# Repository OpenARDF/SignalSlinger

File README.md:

# SignalSlinger

SignalSlinger is an open-source 80-meter radio orienteering (ARDF) transmitter kit for the 3.5 MHz to 3.7 MHz amateur band. It supports classic, sprint, and foxoring events, with a high-accuracy real-time clock for synchronized transmissions and scheduled start and finish times.

## Product Photo

## Documentation

* [User Manual](https://docs.google.com/document/d/1eX7xH3cDyRNS-MVg13EojpP8IB8bDgrdszM48J0sn7k/edit?usp=sharing)
* [Bill of Material](https://docs.google.com/spreadsheets/d/182rCsEmR_KNoESYd0NLeVXOi867AKD0zTovbhvcYbqc/edit?usp=sharing)
* [GitHub Releases](https://github.com/OpenARDF/SignalSlinger/releases)

## Availability

SignalSlinger is available in kit form from Backwoods Orienteering Klub. [Order the SignalSlinger Transmitter Kit](https://backwoodsok.org/store/SignalSlinger-Transmitter-Kit-p799230332) or visit the product page for current pricing, availability, shipping information, and kit details.

## Updating Software

This `main` branch corresponds to the current stable firmware release. Download the update file that matches your hardware revision:

* `SignalSlinger-Update-v2.1.0-HW-3.5.hex`
* `SignalSlinger-Update-v2.1.0-HW-3.4.hex`

Use SerialSlinger for normal updates on devices that already support software updates. For first-time bootloader setup, use the matching complete release bundle and an approved programmer over the board's UPDI programming header (`P101`). Always choose the file that matches your hardware revision, and do not modify fuses or disable UPDI outside the documented setup flow.

For complete programming steps, setup-bundle usage, and hardware connection details, see the [User Manual](https://docs.google.com/document/d/1eX7xH3cDyRNS-MVg13EojpP8IB8bDgrdszM48J0sn7k/edit?usp=sharing). If you want current firmware and software development instead of the stable public release, use `Development1`. KiCad schematic, PCB, library, simulation, and model work is collected separately on `Development1-KiCad`. `main` remains linear, while collector pull requests use merge commits so topic and synchronized `main` ancestry are preserved; after a promotion, verify each focused synchronization topic with `just collector-sync-check <collector>`.

## Firmware Development

Firmware source and build scripts live in [`Software/AVR128DA28`](Software/AVR128DA28).

For the current development workflow, start here:

* [`Software/AVR128DA28/CODEX_WORKFLOW.md`](Software/AVR128DA28/CODEX_WORKFLOW.md) for branch and patch-verification expectations
* [`Software/AVR128DA28/RELEASE_WORKFLOW.md`](Software/AVR128DA28/RELEASE_WORKFLOW.md) for release preparation and dual-target asset checks
* [`Software/AVR128DA28/build-firmware.ps1`](Software/AVR128DA28/build-firmware.ps1) for the standard local firmware build
* [`Software/AVR128DA28/verify-firmware-hashes.ps1`](Software/AVR128DA28/verify-firmware-hashes.ps1) for dual-target `.hex` build and SHA256 verification

## Related Projects

* [SignalStreamer](https://github.com/OpenARDF/SignalStreamer), a matching antenna
* [SignalSnagger](https://github.com/OpenARDF/SignalSnagger), a companion receiver project
* [SerialSlinger](https://github.com/OpenARDF/SerialSlinger), a serial terminal and logging companion for SignalSlinger configuration and monitoring

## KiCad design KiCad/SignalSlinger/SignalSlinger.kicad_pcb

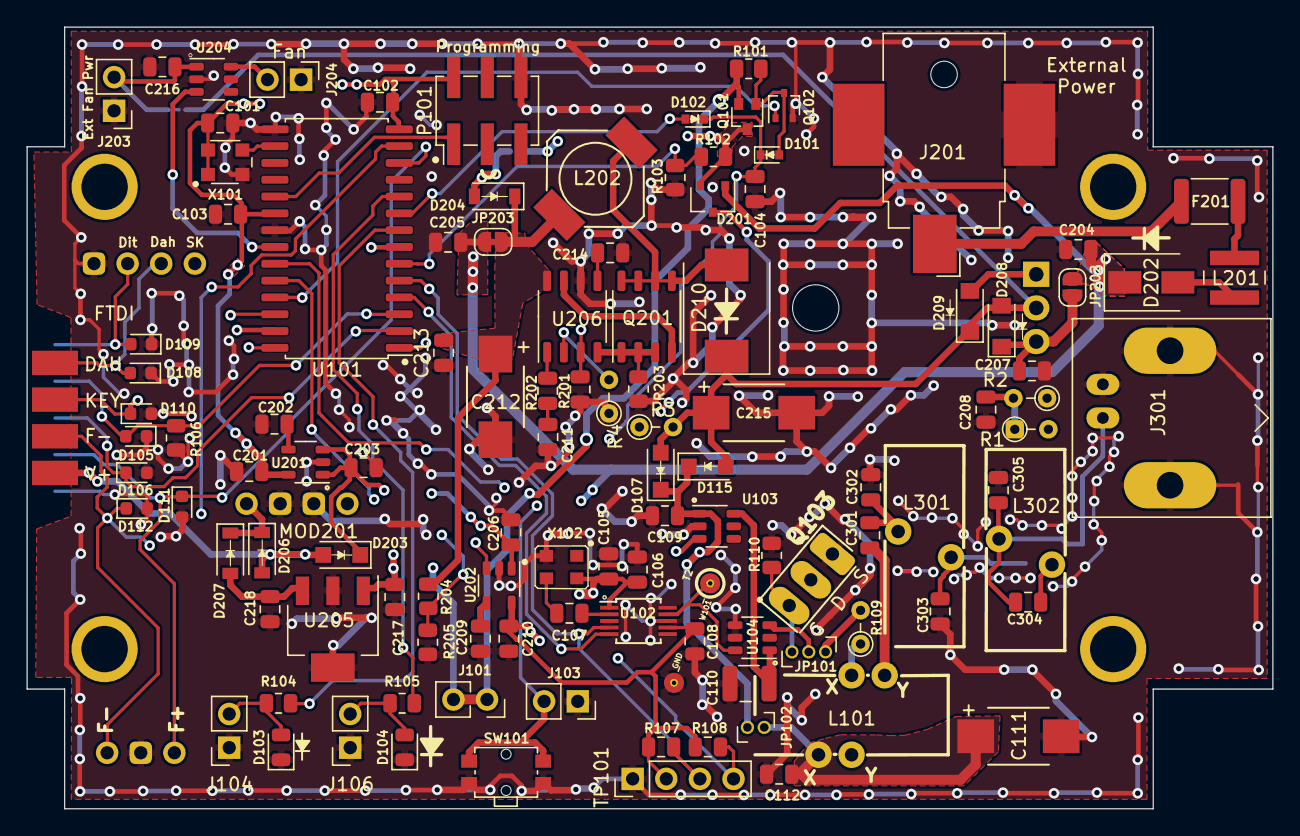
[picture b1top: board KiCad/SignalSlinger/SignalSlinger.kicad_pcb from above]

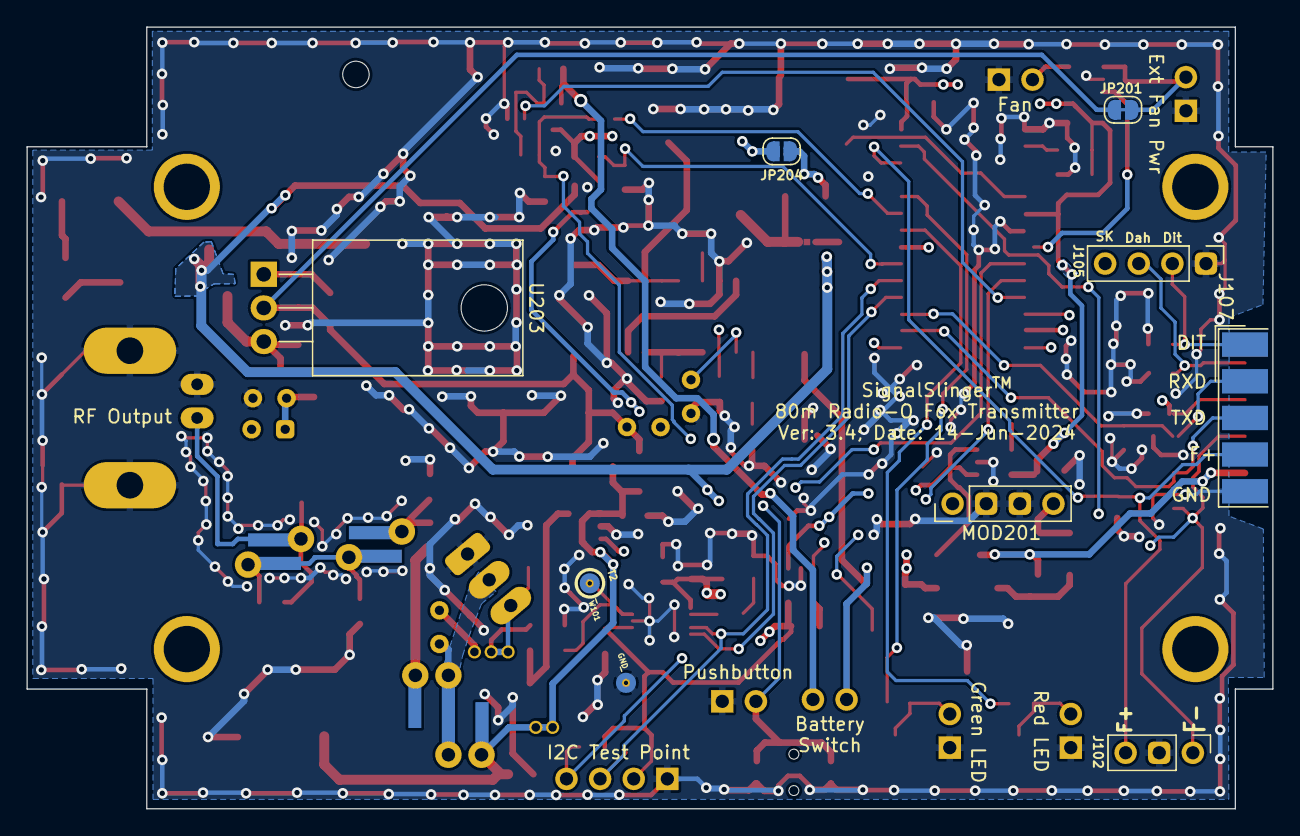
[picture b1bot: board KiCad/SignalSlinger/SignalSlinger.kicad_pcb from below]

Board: 4 copper layers, 94.1 x 59.1 mm, 120 parts (7 on the bottom side), 69 nets.

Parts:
C101, C104, C105, C107, C218: 100nF; C_0805_2012Metric
C102, C103, C106, C108, C112, C204, C217, C301: 470nF; C_0805_2012Metric
C109, C201, C203, C205, C206, C207, C208, C210, C213, C216: 10uF; C_0805_2012Metric
C110: 22uF; C_1210_3225Metric
C111, C212, C215: 47uF low ESR; C_2917
C202, C209, C211: 10nF; C_0805_2012Metric
C214: 1uF; C_0805_2012Metric
C302, C305: 1100pF; C_0805_2012Metric
C303: 1800pF; C_0805_2012Metric
C304: 91pF; C_0805_2012Metric
D101, D102: 1N914WT; D_SOD-523
D103: Red LED; LED_0805_2012Metric
D104: Green LED; LED_0805_2012Metric
D105, D106, D108, D109, D110, D111, D112: ESD9B5.0ST5G_1; D_0603_1608Metric
D107, D115, D203, D204, D206, D207: Schottky Diode; D_SOD-123FL
D201: BAT54C; SC-59
D202: B330A Schottky Diode; D_SMB
D208, D209: 1N4001; D_SOD-123F
D210: B530; D_SMC
F201: 2.6A; Fuse_1812_4532Metric
J101, J103, J104, J106: Conn_01x02; PinSocket_1x02_P2.54mm_Vertical
J102: Conn_01x03; PinHeader_1x03_P2.54mm_Vertical
J105: Conn_01x04; PinHeader_1x04_P2.54mm_Vertical
J107: DB9 Female; DSUB-9_Female_EdgeMount_P2.77mm
J201: Barrel_Jack_Switch; BarrelJack_CUI_PJ-036AH-SMT_Horizontal
J203: External Fan Power; PinHeader_1x02_P2.54mm_Vertical
J204: Controlled Power; PinHeader_1x02_P2.54mm_Vertical
J301: To Antenna; BNC_Amphenol_B6252HB-NPP3G-50_Horizontal
JP101: Jumper_3_Bridged12; Jumper_THT_1x03_Bridged12_P1.27mm_Vertical
JP102: Jumper_2_Bridged; Jumper_THT_1x02_P1.27mm_Vertical
JP201: V-ext disable; SolderJumper-2_P1.3mm_Bridged_RoundedPad1.0x1.5mm
JP202: Ext-to-Linear; SolderJumper-2_P1.3mm_Open_RoundedPad1.0x1.5mm
JP203: Ext-to-Boost; SolderJumper-2_P1.3mm_Bridged_RoundedPad1.0x1.5mm
JP204: Internal_V_Enable; SolderJumper-2_P1.3mm_Open_RoundedPad1.0x1.5mm
L101: 9T #24 Bifilar T50-43; Toroid_T-50A_TH_BF_CT_Vertical
L201: 2.2uH; WPN4020H2R2MT
L202: 6.8uH; CDR7D28MN
L301, L302: 2.7uH; Toroid_T-60_2TH_Vertical
MOD201: AdaFruit Charger; PinHeader_1x04_P2.54mm_Vertical
P101: ISP/PDI; PinHeader_2x03_P2.54mm_Vertical_SMD
Q101: NTS4173PT1G; SOT-323_SC-70
Q102: BSS138W-7-F; SOT-323_SC-70
Q103: IRF610; TO-220_Neutral123_Vertical_LargePads
Q201: RJK0354DSP; SOIC-8_3.9x4.9mm_P1.27mm
R1, R2, R3, R4: TBD; R_Axial_DIN0204_L3.6mm_D1.6mm_P2.54mm_Vertical
R101: 105k; R_0805_2012Metric
R102, R110, R204: 162k; R_0805_2012Metric
R103, R205: 12.4k; R_0805_2012Metric
R104: 1k; R_0805_2012Metric
R105: 220; R_0805_2012Metric
R106: 47k; R_0805_2012Metric
R107, R108, R201, R202: 10k; C_0805_2012Metric
R109: 47 0.5W; R_Axial_DIN0204_L3.6mm_D1.6mm_P2.54mm_Vertical
R203: 0.01 0.5W; R_0805_2012Metric
SW101: SW_SPST; SW_SPST_TL1014BF160QG
TP101: I2C1; PinHeader_1x04_P2.54mm_Vertical
U101: AVR128DA28; SOIC-28W_7.5x17.9mm_P1.27mm
U102: SI5351; MSOP-10_3x3mm_P0.5mm
U103, U204: TPS22810DBVT; SOT-23-6
U104: LM5134; SOT-23-6-LM5134
U201, U202: LP2985-3.3; SOT-23-5
U203: TO-220 ADJ Reg.; TO-220-3_Horizontal_TabDown
U205: uA7805; SOT-223-4
U206: MIC2196YM; SOIC-8_3.9x4.9mm_P1.27mm
W101: T2; Measurement_Point_ScopeProbe_Round-SMD-2sides-Pad_Small
X101: ECS-327TXO-30-TR; Oscillator_SMD_ECS_327TXO
X102: 25 MHz; Crystal_SMD_TXETCLSANF-4Pin

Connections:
+3V3: C101.1, C102.1, C103.2, C201.2, P101.2, U101.14 (AVDD), U101.20 (VDD), U201.5 (VOUT), X101.1 (VC), X101.4 (VDD)
+BATT: J101.2, MOD201.1
+VSW: D201.2 (K), JP204.2 (B), Q101.3 (D), R102.2
BOOST_PWR_ENABLE: R201.2, U101.1 (PA7), U206.3 (EN/UVLO)
CLK1: U102.9 (CLK1), U104.6 (In), W101.1
FET_DRIVER_ENABLE: U101.23 (PA1), U103.3 (EN/UVLO)
Fan_Contr: U101.22 (PA0/EXTCLK), U204.3 (EN/UVLO)
Frequency Down: D112.1 (A1), J102.1, J107.8, U101.13 (PD7)
Frequency Up: D111.1 (A1), J102.3, J107.4, U101.12 (PD6/DAC)
GND: C101.2, C102.2, C103.1, C104.2, C105.2, C106.2, C108.2, C109.1, C110.2, C111.2, C112.1, C201.1, C202.2, C203.1, C204.1, C205.1, C206.1, C207.1, C208.2, C209.2, C210.1, C211.2, C212.2, C213.2, C214.2, C215.2, C216.2, C217.2, C218.2, C302.2, C303.1, C305.2, D103.1 (K), D104.1 (K), D105.1 (A1), D106.2 (A2), D108.1 (A1), D109.1 (A1), D110.2 (A2), D111.2 (A2), D112.2 (A2), J102.2, J103.1, J104.1, J105.1, J106.1, J107.5, J201.2, J203.1, J204.1, J301.2 (Ext), MOD201.2, MOD201.3, P101.6, Q102.2 (S), Q103.3 (S), R2.1, R4.1, R103.1, R106.2, R110.1, R201.1, R203.1, R205.1, SW101.2 (B), TP101.1, U101.15 (GND), U101.21 (GND), U102.8 (GND), U103.2 (GND), U104.4 (Vss), U104.5 (InB), U201.2 (GND), U202.2 (GND), U204.2 (GND), U205.2 (GND), U206.6 (GND), W101.2 (GND), X101.2 (GND), X102.2 (GND)
unnamed: C104.1, D101.1 (K), D102.1 (K), J103.2, SW101.1 (A)
unnamed: C107.1, U102.2 (XA)
unnamed: C107.2, X102.3 (OUT)
unnamed: C109.2, D107.1 (K), D115.1 (K), JP102.1 (A), U103.1 (VIN)
unnamed: C110.1, U103.6 (VOUT), U104.1 (Vdd)
unnamed: C111.1, C112.2, JP102.2 (B), L101.1
unnamed: C202.1, U201.4 (BP)
unnamed: C203.2, C206.2, D201.3 (A), D203.1 (K), U201.1 (VIN), U201.3 (ON/~OFF), U202.1 (VIN)
unnamed: C207.2, D208.1 (K), JP202.1 (A), U203.3 (VI)
unnamed: C208.1, D209.2 (A), R1.1, R2.2, U203.1 (ADJ)
unnamed: C209.1, U202.4 (BP)
unnamed: C211.1, R202.1
unnamed: C212.1, C213.1, D204.1 (K), JP203.2 (B), L202.2, R204.2, U206.8 (VIN)
unnamed: C214.1, U206.5 (VDD)
unnamed: C216.1, J203.2, JP201.2 (B), U204.1 (VIN)
unnamed: C218.1, D207.2 (A), U205.3 (OUT)
unnamed: C301.2, C302.1, L301.1
unnamed: C303.2, C304.2, L301.2, L302.1
unnamed: C304.1, C305.1, J301.1 (In), L302.2
unnamed: D101.2 (A), Q101.1 (G), Q102.3 (D), R101.1
unnamed: D102.2 (A), U101.9 (PD3)
unnamed: D103.2 (A), J104.2, R104.1
unnamed: D104.2 (A), J106.2, R105.1
unnamed: D105.2 (A2), J107.2, R106.1, U101.3 (PC1/RxD1)
unnamed: D106.1 (A1), J107.3, U101.2 (PC0/TxD1)
unnamed: D202.2 (A), L201.2
unnamed: D204.2 (A), JP204.1 (A)
unnamed: D206.1 (K), D207.1 (K), MOD201.4
unnamed: D210.2 (A), L202.1, Q201.5 (D), Q201.6 (D), Q201.7 (D), Q201.8 (D)
unnamed: F201.1, L201.1
unnamed: F201.2, J201.1
unnamed: J101.1, Q101.2 (S), R101.2
unnamed: J204.2, U204.6 (VOUT)
unnamed: JP101.1 (A), Q103.1 (G), R110.2
unnamed: JP101.2 (C), U104.3 (Out)
unnamed: JP101.3 (B), R109.2
unnamed: L101.2 (TAP), Q103.2 (D), R109.1
unnamed: P101.1, U101.19 (UPDI)
unnamed: Q201.1 (S), Q201.2 (S), Q201.3 (S), R203.2, U206.4 (CS)
unnamed: Q201.4 (G), U206.7 (OUTN)
unnamed: R3.1, R4.2, U206.2 (FB)
unnamed: R104.2, U101.8 (PD2)
unnamed: R105.2, U101.10 (PD4)
unnamed: R107.1, TP101.3, U101.5 (PC3/SCL), U102.4 (SCL)
unnamed: R108.1, TP101.4, U101.4 (PC2/SDA), U102.5 (SDA)
unnamed: R202.2, U206.1 (COMP)
unnamed: U101.16 (PF0/XTAL32k1), X101.3 (OUT)
Paddle Dah: D108.2 (A2), J105.3, J107.6, U101.27 (PA5/RxD0)
Paddle_Dit: D109.2 (A2), J105.2, J107.1, U101.26 (PA4/TxD0)
Power_enable: Q102.1 (G), U101.25 (PA3)
RF_Raw: C301.1, L101.3
Straightkey: D110.1 (A1), J105.4, J107.7, U101.28 (PA6)
V3V3_PWR_ENABLE: U101.24 (PA2), U202.3 (ON/~OFF)
V+_Charging: D203.2 (A), D206.2 (A), J107.9
VDD: C105.1, C106.1, C108.1, C210.2, R107.2, R108.2, TP101.2, U102.1 (VDD), U102.7 (VDDO), U202.5 (VOUT), X102.4 (Vcc)
V_ext: C204.2, C205.2, C217.1, D201.1 (K), D202.1 (K), JP202.2 (B), JP203.1 (A), U205.1 (IN)
Vbat: R102.1, R103.2, U101.6 (PD0/AIN0)
Vdrive: C215.1, D107.2 (A), D115.2 (A), D208.2 (A), D209.1 (K), D210.1 (K), JP201.1 (A), R1.2, R3.2, U203.2 (VO)
Vext: R204.1, R205.2, U101.7 (PD1)

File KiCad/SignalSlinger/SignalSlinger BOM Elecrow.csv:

Reference,Manufacturer Part number,Qty,Original,Description,Purchase Link,Value,Datasheet,Manufacturer,Footprint,Digi-Key Part No.,LCSC Part Number
"C101,C104,C105,C107,C218",CL21B104KACNNNC,5,N,CAP CER 0.1UF 25V X7R 0805,https://www.digikey.com/short/q2f22qnq,100nF,~,Samsung Electro-Mechanics,Capacitor_SMD:C_0805_2012Metric,1276-1099-1-ND,C29926
"C102,C103,C106,C108,C112,C204,C217,C301",08051C474K4Z2A,8,N,CAP CER 0.47UF 100V X7R 0805,https://www.digikey.com/products/en?keywords=478-9924-1-ND,470nF,,AVX Corporation,Capacitor_SMD:C_0805_2012Metric,478-9924-1-ND,C342818
"C109,C201,C203,C205,C206,C207,C208,C210,C216,C299",C2012X5R1V106K125AC,10,N,CAP CER 10UF 35V X5R 0805,https://www.digikey.com/short/p8qdn4mp,10uF,,TDK Corporation,Capacitor_SMD:C_0805_2012Metric,445-14418-1-ND,C3843628
C110,CL32A226MAJNNNE,1,N,CAP CER 22UF 25V X5R 1210,https://www.digikey.com/products/en?keywords=1276-3373-1-ND,22uF,,Samsung Electro-Mechanics,Capacitor_SMD:C_1210_3225Metric,1276-3373-1-ND,C337455
"C111,C215",T495X476K020ATE150,2,N,CAP TANT 47UF 10% 20V 2917,https://www.digikey.com/products/en?keywords=399-3904-1-ND,47uF low ESR,,KEMET,SignalSlinger_Footprints:C_2917,399-3904-1-ND,C122333
"C202,C209",C0805C103J5GEC7800,2,N,CAP CER 0805 10NF 50V C0G 5%,https://www.digikey.com/short/qd893213,10nF,,KEMET,Capacitor_SMD:C_0805_2012Metric,399-C0805C103J5GEC7800CT-ND,C3887673
"C302,C305",GRM2195C2A112JA01D,2,N,"1100 pF ±5% 100V Ceramic Capacitor C0G, NP0 0805 (2012 Metric)",https://www.digikey.com/en/products/detail/murata-electronic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,1100pF,,Murata Electronics,Capacitor_SMD:C_0805_2012Metric,GRM2195C2A112JA01D-ND,
C303,GCM2165C2A182GA16D,1,N,Multilayer Ceramic Capacitors MLCC - SMD/SMT 1800 pF 100 VDC 2% 0805 C0G (NP0) AEC-Q200,https://www.digikey.com/en/products/detail/murata-electronic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,1800pF,,Murata Electronics,Capacitor_SMD:C_0805_2012Metric,,
C304,08051A910FAT2A,1,N,Multilayer Ceramic Capacitors MLCC - SMD/SMT 100V 91pF C0G 0805 1%,https://www.digikey.com/en/products/detail/kyocera-avx/08051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,91pF,,KYOCERA AVX,Capacitor_SMD:C_0805_2012Metric,,
"D101,D102",1N4148WT-7,2,N,DIODE GEN PURP 80V 125MA SOD523,https://www.digikey.com/en/products/detail/diodes-incorporat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,1N914WT,,Diodes Incorporated,Diode_SMD:D_SOD-523,1N4148WTDICT-ND,C83482
D103,LTST-C170KRKT,1,N,LED RED CLEAR SMD,https://www.digikey.com/en/products/detail/liteon/LTST-C170K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,Red LED,~,Lite-On Inc.,LED_SMD:LED_0805_2012Metric,160-1415-1-ND,C94868
D104,LTST-C170KGKT,1,N,LED GREEN CLEAR SMD,https://www.digikey.com/en/products/detail/liteon/LTST-C170K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,Green LED,~,Lite-On Inc.,LED_SMD:LED_0805_2012Metric,160-1414-1-ND,C98221
"D105,D106,D108,D109,D110,D111,D112",CG0603MLC-05LE,7,N,VARISTOR 0603,https://www.digikey.com/products/en?keywords=CG0603MLC-05LECT-ND,ESD9B5.0ST5G_1,,Bourns Inc.,Diode_SMD:D_0603_1608Metric,CG0603MLC-05LECT-ND,C316054
"D107,D115,D203,D204,D206,D207","CRS09(TE85L,Q,M)",6,N,DIODE SCHOTTKY 30V 1.5A SOD-123FL,https://www.digikey.com/en/products/detail/toshiba-semicondu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,Schottky Diode,,Toshiba Semiconductor and Storage,SignalSlinger_Footprints:D_SOD-123FL,CRS09QCT-ND,
D201,"BAT54C,215",1,N,DIODE ARRAY SCHOTTKY 30V SOT23,https://www.digikey.com/en/products/detail/nexperia-usa-inc/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,BAT54C,,Nexperia USA Inc.,Package_TO_SOT_SMD:SC-59,1727-2902-1-ND,C37704
D202,S3AB-13-F,1,N,DIODE GEN PURP 50V 3A SMB,https://www.digikey.com/en/products/detail/diodes-incorporat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,B330A Schottky Diode,,Diodes Incorporated,Diode_SMD:D_SMA,S3AB-FDICT-ND,
"D208,D209",HS1AFL,2,N,DIODE GEN PURP 50V 1A SOD123F,https://www.digikey.com/en/products/detail/taiwan-semiconduc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,1N4001,,Taiwan Semiconductor Corporation,Diode_SMD:D_SOD-123F,HS1AFLCT-ND,
F201,0ZCG0260BF2B,1,N,PTC RESET FUSE 16V 2.6A 1812,https://www.digikey.com/en/products/detail/bel-fuse-inc/0ZCG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,2.6A,~,Bel Fuse Inc.,Fuse:Fuse_1812_4532Metric,0ZCG0260BF2B,
J201,PJ-036AH-SMT-TR,1,N,CONN PWR JACK 2X5.5MM SOLDER,https://www.digikey.com/en/products/detail/cui-devices/PJ-03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,Barrel_Jack_Switch,~,CUI Devices,Connector_BarrelJack:BarrelJack_CUI_PJ-036AH-SMT_Horizontal,CP-036AHPJCT-ND,
L201,WPN4020H2R2MT,1,N,FIXED IND 2.2UH 4.3A 48MOHM SMD,https://www.digikey.com/en/products/detail/shenzhen-sunlord-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,2.2uH,,"Shenzhen Sunlord Electronics Co., Ltd.",SignalSlinger_Footprints:WPN4020H2R2MT,3442-WPN4020H2R2MTCT-ND,
P101,95278-101A06LF,1,N,CONN HEADER SMD 6POS 2.54MM,https://www.digikey.com/products/en?keywords=609-3487-1-ND,ISP/PDI,,Amphenol ICC (FCI),Connector_PinHeader_2.54mm:PinHeader_2x03_P2.54mm_Vertical_SMD,609-3487-1-ND,C178294
Q101,NTS4173PT1G,1,N,MOSFET P-CH 30V 1.2A SC70-3,https://www.digikey.com/short/j97zqh7v,NTS4173PT1G,,ONSEMI,Package_TO_SOT_SMD:SOT-323_SC-70,NTS4173PT1GOSCT-ND,
Q102,BSS138W-7-F,1,N,MOSFET N-CH 50V 200MA SOT323,https://www.digikey.com/short/m8f8nn79,BSS138W-7-F,,Diodes Incorporated,Package_TO_SOT_SMD:SOT-323_SC-70,BSS138W-FDICT-ND,C24553
R101,RC0805FR-07105KL,1,N,RES 105K OHM 1% 1/8W 0805,https://www.digikey.com/en/products/detail/yageo/RC0805FR-07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,105k,,YAGEO,Resistor_SMD:R_0805_2012Metric,311-105KCRCT-ND,C273877
"R102,R110,R204",RC0805FR-07162KL,3,N,RES 162K OHM 1% 1/8W 0805,https://www.digikey.com/en/products/detail/yageo/RC0805FR-07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,162k,,YAGEO,Resistor_SMD:R_0805_2012Metric,311-162KCRCT-ND,C273888
"R103,R205",RC0805FR-0712K4L,2,N,RES 12.4K OHM 1% 1/8W 0805,https://www.digikey.com/en/products/detail/yageo/RC0805FR-07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,12.4k,,YAGEO,Resistor_SMD:R_0805_2012Metric,311-12.4KCRCT-ND,C137595
R104,RMCF0805FT1K00,1,N,RES 1K OHM 1% 1/8W 0805,https://www.digikey.com/en/products/detail/stackpole-electro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,1k,,Stackpole Electronics Inc,Resistor_SMD:R_0805_2012Metric,RMCF0805FT1K00CT-ND,C17513
R105,RC0805FR-10220RL,1,N,RES 220 OHM 1% 1/8W 0805,https://www.digikey.com/en/products/detail/yageo/rc0805fr-10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,220,,Yageo,Resistor_SMD:R_0805_2012Metric,13-RC0805FR-10220RLCT-ND,
R106,RC0805FR-0747KL,1,N,RES 47K OHM 1% 1/8W 0805,https://www.digikey.com/en/products/detail/yageo/RC0805FR-07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,47k,,YAGEO,Resistor_SMD:R_0805_2012Metric,311-47.0KCRCT-ND,C126351
"R107,R108",RNCP0805FTD10K0,2,N,RES 10K OHM 1% 1/4W 0805,https://www.digikey.com/en/products/detail/stackpole-electro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,10k,,Stackpole Electronics Inc,Resistor_SMD:R_0805_2012Metric,RNCP0805FTD10K0CT-ND,C2441435
U101,AVR128DA28T-E/SO,1,Y,IC MCU 8BIT 128KB FLASH 28SOIC,https://www.digikey.com/short/781hqp8f,AVR128DA28,http://ww1.microchip.com/downloads/en/DeviceDoc/doc7707.pdf,Microchip Technology,SignalSlinger_Footprints:SOIC-28W_7.5x17.9mm_P1.27mm,150-AVR128DA28T-E/SOCT-ND,C1870730
U102,SI5351A-B-GT,1,Y,IC CLK GENERATOR 200MHZ 10MSOP,https://www.digikey.com/products/en?keywords=336-2399-5-ND,SI5351,http://www.silabs.com/Support%20Documents/TechnicalDocs/Si53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,Silicon Labs,Package_SO:MSOP-10_3x3mm_P0.5mm,336-2399-5-ND,C529366
"U103,U204,U206",TPS22810DBVT,3,N,Power Switch/Driver 1:1 N-Channel 2A SOT-23-6,https://www.digikey.com/products/en?keywords=296-45304-1-ND,TPS22810DBVT,http://www.ti.com/lit/ds/symlink/tps22810.pdf,Texas Instruments,Package_TO_SOT_SMD:SOT-23-6,296-45304-1-ND,C2680364
U104,LM5134BMFX/NOPB,1,N,IC GATE DRVR LOW-SIDE SOT23-6,https://www.digikey.com/products/en?keywords=296-40244-1-ND,LM5134,,Texas Instruments,SignalSlinger_Footprints:SOT-23-6-LM5134,296-40244-1-ND,C2677086
"U201,U202",LP2985A-33DBVR,2,N,IC REG LINEAR 3.3V 150MA SOT23-5,https://www.digikey.com/short/vr2m3rjp,LP2985-3.3,,Texas Instruments,Package_TO_SOT_SMD:SOT-23-5,296-18479-1-ND,C89826
U205,UA78M05IDCYR,1,N,IC REG LINEAR 5V 500MA SOT223-4,https://www.digikey.com/en/products/detail/texas-instruments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,uA7805,http://www.ti.com/lit/ds/symlink/ua78.pdf,Texas Instruments,SignalSlinger_Footprints:SOT-223-4,296-17616-1-ND,
X101,ECS-327TXO-30-TR,1,N,OSC TCXO 32.768KHZ 3.0V SMD,https://www.digikey.com/en/products/detail/ecs-inc/ecs-327tx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,ECS-327TXO-30-TR,,ECS Inc.,SignalSlinger_Footprints:Oscillator_SMD_ECS_327TXO,50-ECS-327TXO-30-CT-ND,
X102,TXETCLSANF-25.000000,1,Y,XTAL OSC TCXO 25.0000MHZ SNWV,https://www.digikey.com/products/en?keywords=1664-1273-1-ND,25 MHz,,Taitien,SignalSlinger_Footprints:Crystal_SMD_TXETCLSANF-4Pin,1664-1273-1-ND,

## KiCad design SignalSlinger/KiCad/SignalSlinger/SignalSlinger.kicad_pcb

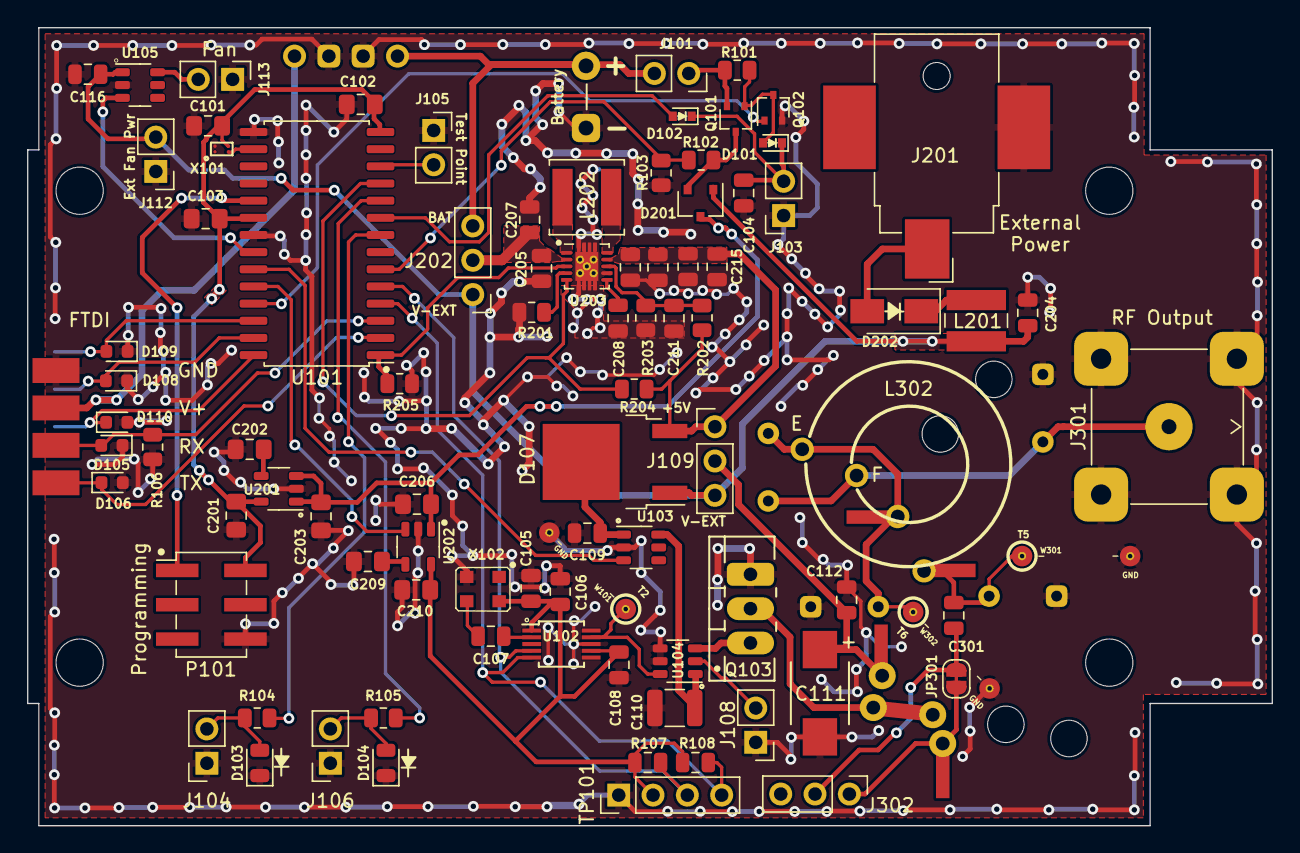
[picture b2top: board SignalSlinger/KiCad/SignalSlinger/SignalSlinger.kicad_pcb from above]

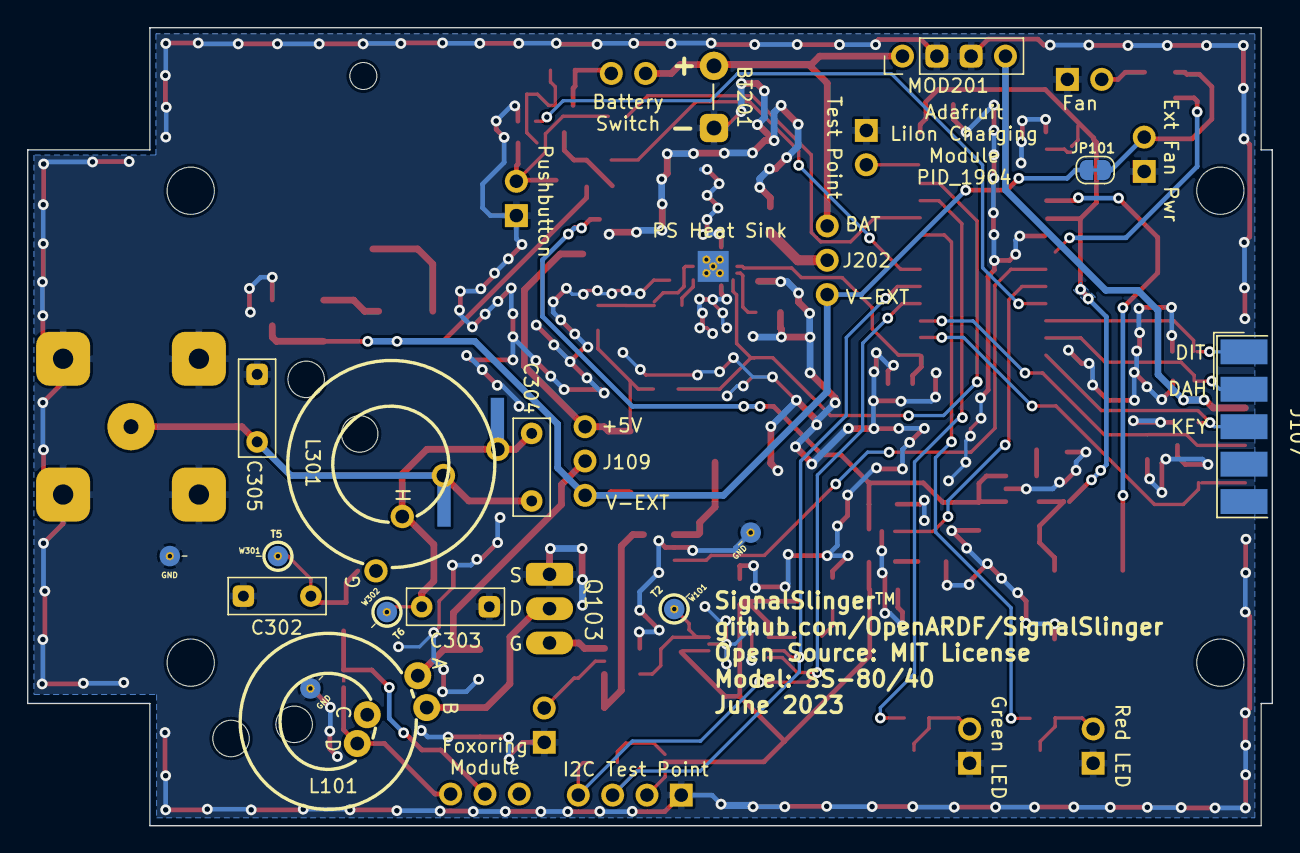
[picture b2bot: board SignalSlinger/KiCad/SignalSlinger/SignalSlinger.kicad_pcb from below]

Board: 2 copper layers, 92.1 x 59.1 mm, 99 parts (10 on the bottom side), 60 nets.

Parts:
BT201: LiIon Cell; SolderWire-0.5sqmm_1x02_P4.6mm_D0.9mm_OD2.1mm
C101: 100nF; C_0805_2012Metric_Pad1.18x1.45mm_HandSolder
C102, C103: 470nF; C_0805_2012Metric_Pad1.18x1.45mm_HandSolder
C104, C105, C107, C208: 100nF; C_0805_2012Metric
C106, C108, C112, C204, C301: 470nF; C_0805_2012Metric
C109, C116, C205, C207: 10uF; C_0805_2012Metric
C110: 22uF; C_1210_3225Metric
C111: 47uF low ESR; C_2917
C201, C203, C206, C210: 10uF; C_0805_2012Metric_Pad1.18x1.45mm_HandSolder
C202, C209: 10nF; C_0805_2012Metric_Pad1.18x1.45mm_HandSolder
C211: 10pF; C_0805_2012Metric
C212: 1uF; C_0805_2012Metric
C213, C214, C215: 22uF; C_0805_2012Metric
C302, C305: 1100pF; C_Rect_L7.0mm_W2.5mm_P5.00mm
C303: 1800pF; C_Rect_L7.0mm_W2.5mm_P5.00mm
C304: 91pF; C_Rect_L7.0mm_W2.5mm_P5.00mm
D101, D102: 1N914WT; D_SOD-523
D103: Red LED; LED_0805_2012Metric
D104: Green LED; LED_0805_2012Metric
D105, D106, D108, D109, D110: ESD9B5.0ST5G_1; D_0603_1608Metric
D107: MBRD10100CT; TO-252-2
D201: BAT54C; SC-59
D202: D_Schottky_Filled; D_SMA
J101, J103, J104, J105, J106: Conn_01x02; PinSocket_1x02_P2.54mm_Vertical
J107: DB9 Female; DSUB-9_Female_EdgeMount_P2.77mm
J108: Conn_01x02; PinHeader_1x02_P2.54mm_Vertical
J109, J202, J302: Conn_01x03; PinHeader_1x03_P2.54mm_Vertical
J112: External Power Source; PinHeader_1x02_P2.54mm_Vertical
J113: Controlled Power; PinHeader_1x02_P2.54mm_Vertical
J201: Barrel_Jack_Switch; BarrelJack_CUI_PJ-036AH-SMT_Horizontal
J301: To Antenna; BNC_TEConnectivity_1478035_Horizontal
JP101: V-ext disable; SolderJumper-2_P1.3mm_Bridged_RoundedPad1.0x1.5mm
JP301: QRP disable; SolderJumper-2_P1.3mm_Bridged_RoundedPad1.0x1.5mm
L101: 9T #24 Bifilar T50-43; Toroid_T-50A_TH_BF_CT
L201: 2.2uH; L_Wuerth_WE-LQS
L202: 1uH; L_Bourns_SRN5040TA
L301, L302: 2.7uH; Toroid_T-60_2TH
MOD201: AdaFruit Charger; PinHeader_1x04_P2.54mm_Vertical
P101: ISP/PDI; PinHeader_2x03_P2.54mm_Vertical_SMD
Q101: BSS84W-7-F; SOT-323_SC-70
Q102: BSS138W-7-F; SOT-323_SC-70
Q103: IRF610; TO-220_Neutral123_Vertical_LargePads
R101, R201, R203, R205: 105k; R_0805_2012Metric
R102: 162k; R_0805_2012Metric
R103: 12.4k; R_0805_2012Metric
R104, R105: 1k; R_0805_2012Metric
R106: 47k; R_0805_2012Metric
R107, R108: 10k; C_0805_2012Metric
R202, R204: 1M; R_0805_2012Metric
TP101: I2C1; PinHeader_1x04_P2.54mm_Vertical
U101: AVR128DA28; SOIC-28W_7.5x17.9mm_P1.27mm
U102: SI5351; MSOP-10_3x3mm_P0.5mm
U103, U105: TPS22810DBVT; SOT-23-6
U104: LM5134; SOT-23-6-LM5134
U201, U202: LP2985-3.3; SOT-23-5
U203: TPS63060; Texas_S-PWSON-N10_ThermalVias
W101: T2; Measurement_Point_ScopeProbe_Round-SMD-2sides-Pad_Small
W301: T5; Measurement_Point_ScopeProbe_Round-SMD-2sides-Pad_Small
W302: T6; Measurement_Point_ScopeProbe_Round-SMD-2sides-Pad_Small
X101: SIT1566AC TCO; Oscillator_SMD_SiTime_SIT1566AC-4Pin_BGA
X102: 25 MHz; Crystal_SMD_TXETCLSANF-4Pin

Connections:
+3V3: C101.1, C102.1, C103.2, C201.2, P101.2, U101.14 (AVDD), U101.20 (VDD), U201.5 (VOUT), X101.3 (Vdd)
+5V: C212.1, C213.2, C214.2, C215.2, D107.3 (K), J109.1, R202.1, R204.1, U203.9 (VOUT)
+BATT: BT201.1 (+), J101.2, J202.3, MOD201.1
+VSW: D201.2 (K), Q101.3 (D), R102.2
B/B_PS_Enable: R205.1, U101.1 (PA7), U203.3 (EN)
CLK1: U102.9 (CLK1), U104.6 (In), W101.1
FET_DRIVER_ENABLE: U101.23 (PA1), U103.3 (EN/UVLO)
Fan_Contr: U101.22 (PA0/EXTCLK), U105.3 (EN/UVLO)
GND: BT201.2 (-), C101.2, C102.2, C103.1, C104.2, C105.2, C106.2, C108.2, C109.1, C110.2, C111.2, C112.2, C116.2, C201.1, C202.2, C203.1, C204.1, C205.1, C206.1, C207.1, C208.2, C209.2, C210.1, C211.2, C212.2, C213.1, C214.1, C215.1, C302.2, C303.1, C305.2, D103.1 (K), D104.1 (K), D105.1 (A1), D106.2 (A2), D108.1 (A1), D109.1 (A1), D110.2 (A2), J103.1, J104.1, J105.1, J106.1, J107.6, J108.1, J112.1, J113.1, J201.2, J301.2 (Ext), MOD201.2, MOD201.3, P101.6, Q102.2 (S), Q103.3 (S), R103.1, R106.2, R201.2, R203.2, R205.2, TP101.1, U101.15 (GND), U101.21 (GND), U102.8 (GND), U103.2 (GND), U104.4 (Vss), U104.5 (InB), U105.2 (GND), U201.2 (GND), U202.2 (GND), U203.7 (GND), U203.11 (PGND), W101.2 (GND), W301.2 (GND), W302.2 (GND), X101.4 (GND), X102.2 (GND)
unnamed: C104.1, D101.1 (K), D102.1 (K), J103.2
unnamed: C107.1, U102.2 (XA)
unnamed: C107.2, X102.3 (OUT)
unnamed: C109.2, D107.2 (A), U103.1 (VIN)
unnamed: C110.1, U103.6 (VOUT), U104.1 (Vdd)
unnamed: C111.1, C112.1, J109.2, L101.1
unnamed: C116.1, J112.2, JP101.2 (B), U105.1 (VIN)
unnamed: C202.1, U201.4 (BP)
unnamed: C203.2, C206.2, D201.3 (A), U201.1 (VIN), U201.3 (ON/~OFF), U202.1 (VIN)
unnamed: C205.2, C207.2, J202.2, U203.2 (VIN)
unnamed: C208.1, U203.6 (VAUX)
unnamed: C209.1, U202.4 (BP)
unnamed: C211.1, R202.2, R203.1, U203.8 (FB)
unnamed: C301.1, J302.2, JP301.2 (B)
unnamed: C301.2, C302.1, L301.1, W301.1
unnamed: C303.2, C304.2, L301.2, L302.1, W302.1
unnamed: C304.1, C305.1, J301.1 (In), L302.2
unnamed: D101.2 (A), Q101.1 (G), Q102.3 (D), R101.1
unnamed: D102.2 (A), U101.9 (PD3)
unnamed: D103.2 (A), J104.2, R104.1
unnamed: D104.2 (A), J106.2, R105.1
unnamed: D105.2 (A2), J107.8, R106.1, U101.3 (PC1/RxD1)
unnamed: D106.1 (A1), J107.9, U101.2 (PC0/TxD1)
unnamed: J101.1, Q101.2 (S), R101.2
unnamed: J105.2, U101.12 (PD6/DAC)
unnamed: J108.2, U104.2 (Pilot)
unnamed: J113.2, U105.6 (VOUT)
unnamed: D202.2 (A), J201.1
unnamed: L101.2 (TAP), Q103.2 (D)
unnamed: D202.1 (K), L201.1
unnamed: L202.1, U203.1 (L1)
unnamed: L202.2, U203.10 (L2)
unnamed: P101.1, U101.19 (UPDI)
unnamed: Q103.1 (G), U104.3 (Out)
unnamed: R104.2, U101.8 (PD2)
unnamed: R105.2, U101.10 (PD4)
unnamed: R107.1, TP101.3, U101.5 (PC3/SCL), U102.4 (SCL)
unnamed: R108.1, TP101.4, U101.4 (PC2/SDA), U102.5 (SDA)
unnamed: R201.1, U203.4 (PS/SYNC)
unnamed: U101.16 (PF0/XTAL32k1), X101.2 (OUT)
Paddle Dah: D108.2 (A2), J107.2, U101.27 (PA5/RxD0)
Paddle_Dit: D109.2 (A2), J107.1, U101.26 (PA4/TxD0)
Power_Good: R204.2, U101.11 (PD5), U203.5 (PG)
Power_enable: Q102.1 (G), U101.25 (PA3)
RF_Raw: J302.1, JP301.1 (A), L101.3
Straightkey: D110.1 (A1), J107.3, U101.28 (PA6)
V3V3_PWR_ENABLE: U101.24 (PA2), U202.3 (ON/~OFF)
V+_Charging: J107.7, MOD201.4
VDD: C105.1, C106.1, C108.1, C210.2, R107.2, R108.2, TP101.2, U102.1 (VDD), U102.7 (VDDO), U202.5 (VOUT), X102.4 (Vcc)
V_ext: C204.2, D107.1 (K), D201.1 (K), J109.3, J202.1, JP101.1 (A), L201.2
Vbat: R102.1, R103.2, U101.6 (PD0/AIN0)

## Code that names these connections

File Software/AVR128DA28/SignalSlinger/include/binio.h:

/*
 *  MIT License
 *
 *  Copyright (c) 2026 DigitalConfections
 *
 *  Permission is hereby granted, free of charge, to any person obtaining a copy
 *  of this software and associated documentation files (the "Software"), to deal
 *  in the Software without restriction, including without limitation the rights
 *  to use, copy, modify, merge, publish, distribute, sublicense, and/or sell
 *  copies of the Software, and to permit persons to whom the Software is
 *  furnished to do so, subject to the following conditions:
 *
 *  The above copyright notice and this permission notice shall be included in all
 *  copies or substantial portions of the Software.
 *
 *  THE SOFTWARE IS PROVIDED "AS IS", WITHOUT WARRANTY OF ANY KIND, EXPRESS OR
 *  IMPLIED, INCLUDING BUT NOT LIMITED TO THE WARRANTIES OF MERCHANTABILITY,
 *  FITNESS FOR A PARTICULAR PURPOSE AND NONINFRINGEMENT. IN NO EVENT SHALL THE
 *  AUTHORS OR COPYRIGHT HOLDERS BE LIABLE FOR ANY CLAIM, DAMAGES OR OTHER
 *  LIABILITY, WHETHER IN AN ACTION OF CONTRACT, TORT OR OTHERWISE, ARISING FROM,
 *  OUT OF OR IN CONNECTION WITH THE SOFTWARE OR THE USE OR OTHER DEALINGS IN THE
 *  SOFTWARE.
 */

/*
 * Board-level digital I/O and shared hardware-resource control.
 *
 * This module contains support functions for:
 * - configuring GPIO directions, pull-ups, and default output states
 * - debouncing sampled switch inputs
 * - arbitrating shared load-switch style resources between firmware clients
 *
 * Higher-level event logic and policy decisions belong elsewhere.
 */

#ifndef __BINIO_H__
#define __BINIO_H__

#include "defs.h"

/* PORTA *************************************************************************************/
#ifdef HW_TARGET_3_5
#define COOLING_FAN_ENABLE 7
#else
#define BOOST_PWR_ENABLE 7
#endif

#define STRAIGHTKEY 6 /* Straight key */
#define PADDLE_DAH 5  /* Paddle Dah */
#define PADDLE_DIT 4  /* Paddle Dit */
#define POWER_ENABLE 3
#define V3V3_PWR_ENABLE 2
#define FET_DRIVER_ENABLE 1
/*
 * Hardware topology note:
 * - When HW_TARGET_3_5 is defined, the board has separate switched outputs for
 *   external-battery control (AUX_SWITCH_ENABLE below) and cooling-fan control
 *   (COOLING_FAN_ENABLE above).
 * - When HW_TARGET_3_5 is not defined, the board has only one auxiliary switched
 *   output on this pin. At runtime that shared output is used either for
 *   external-battery/charging support or as a temperature-controlled fan switch.
 */
#define AUX_SWITCH_ENABLE 0

/* PORTC *************************************************************************************/
#define SI5351_SCL 3
#define SI5351_SDA 2
#define SERIAL_RX 1
#define SERIAL_TX 0

/* PORTD *************************************************************************************/
#define unusedD7 7
#define DAC_OUTPUT 6
#define unusedD5 5
#define LED_GREEN 4
#define SWITCH 3
#define LED_RED 2
#define VBAT_EXT 1
#define VBAT_INT 0

/* PORTF *************************************************************************************/
#define unusedF6 6
#define X32KHZ_SQUAREWAVE 0
#define unusedF1 1

enum hardwareResourceClients
{
	INTERNAL_BATTERY_CHARGING,
	TRANSMITTER,
	BATTERY_MEASUREMENT,
	NUMBER_OF_LS_CONTROLLERS,
	INITIALIZE_LS,
	RE_APPLY_LS_STATE
};

/**
 * Initialize board-level GPIO directions, pull modes, and default output states.
 *
 * This should be called during firmware startup before any higher-level module
 * assumes ownership of LEDs, switches, keyed outputs, or load-switch resources.
 */
void BINIO_init(void);

/**
 * Sample raw input ports and update the debounced input snapshots.
 *
 * The debounce filter uses a short history window, so callers should invoke this
 * periodically from a timer-driven context rather than in a tight polling loop.
 */
void debounce(void);

/**
 * Return the latest debounced snapshot of PORTD input bits.
 *
 * @return Debounced PORTD level bitmap.
 */
uint8_t portDdebouncedVals(void);

/**
 * Qualify the main front-panel switch using the debounce path.
 *
 * The function seeds the debounce history from the current raw port state so it
 * can make a one-shot switch decision without relying on older samples.
 *
 * @return true when the debounced switch input is in the closed/active state.
 */
bool debouncedSwitchIsClosed(void);

/**
 * Request or release the FET-driver load switch on behalf of a firmware client.
 *
 * @param onoff Desired client state.
 * @param sender Client requesting the change.
 * @return The effective shared output state after arbitration.
 */
bool setFETDriverLoadSwitch(bool onoff, hardwareResourceClients sender);

/**
 * Drive the FET-driver enable pin directly.
 *
 * This is the low-level pin-control primitive used by the shared arbitration
 * wrapper above.
 *
 * @param state Desired pin state.
 */
void fet_driver(bool state);

/**
 * Read back the FET-driver enable output state.
 *
 * @return true when the FET-driver enable output is asserted.
 */
bool get_fet_driver(void);

/**
 * Read back the signal-generator 3.3 V enable output state.
 *
 * @return true when the shared 3.3 V rail enable output is asserted.
 */
bool get_V3V3_enable(void);

/**
 * Re-apply the current external-battery load-switch arbitration state.
 *
 * @param client Caller identifier, retained for API compatibility.
 * @return The effective shared output state after arbitration is re-applied.
 */
bool setExtBatLoadSwitch(hardwareResourceClients client);

/**
 * Request or release the external-battery auxiliary switch on behalf of a client.
 *
 * @param onoff Desired client state.
 * @param sender Client requesting the change.
 * @return The effective shared output state after arbitration.
 */
bool setExtBatLoadSwitch(bool onoff, hardwareResourceClients sender);

/* Transmission/charging demand, excluding a temporary voltage probe. */
bool externalBatteryPowerRequested(void);

/**
 * Request or release the signal-generator supply on behalf of a firmware client.
 *
 * @param onoff Desired client state.
 * @param sender Client requesting the change.
 * @return The effective shared output state after arbitration.
 */
bool setSignalGeneratorEnable(bool onoff, hardwareResourceClients sender);

#ifdef HW_TARGET_3_5
/**
 * Drive the dedicated cooling-fan auxiliary output.
 *
 * @param onoff Desired fan-switch state.
 */
void setCoolingFanLSEnable(bool onoff);

/**
 * Read back the dedicated cooling-fan auxiliary output state.
 *
 * @return true when the fan-switch output is asserted.
 */
bool getCoolingFanLSEnable(void);
#else
/**
 * Drive the legacy boost-regulator enable output.
 *
 * @param onoff Desired boost-enable state.
 * @return The same state that was requested.
 */
bool setBoostEnable(bool onoff);
#endif

/**
 * Read back the external-battery auxiliary output state.
 *
 * @return true when the auxiliary switch output is asserted.
 */
bool getExtBatLSEnable(void);

#endif //__BINIO_H__

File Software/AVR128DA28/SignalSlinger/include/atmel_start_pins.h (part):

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*************************************************************************************/

/**
 * \brief Set PA0 pull mode
 *
 * Configure pin to pull up, down or disable pull mode, supported pull
 * modes are defined by device used
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}

/**
 * \brief Set PA0 data direction
 *
 * Select if the pin data direction is input, output or disabled.
 * If disabled state is not possible, this function throws an assert.
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}

/**
 * \brief Set PA0 input/sense configuration
 *
 * Enable/disable PA0 digital input buffer and pin change interrupt,
 * select pin interrupt edge/level sensing mode
 *
 * \param[in] isc PORT_ISC_INTDISABLE_gc    = Iterrupt disabled but input buffer enabled
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}

/**
 * \brief Set PA0 inverted mode
 *
 * Enable or disable inverted I/O on a pin
 *
 * \param[in] inverted true  = I/O on PA0 is inverted
 *                     false = I/O on PA0 is not inverted
 */
static inline void PA0_set_inverted(const bool inverted)
{
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}

/**
 * \brief Set PA0 level
 *
 * Sets output level on a pin
 *
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}

/**
 * \brief Toggle output level on PA0
 *
 * Toggle the pin level
 */
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}

/**
 * \brief Get level on PA0
 *
 * Reads the level on a pin
 */
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}

/**
 * \brief Set PA1 pull mode
 *
 * Configure pin to pull up, down or disable pull mode, supported pull
 * modes are defined by device used
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}

/**
 * \brief Set PA1 data direction
 *
 * Select if the pin data direction is input, output or disabled.
 * If disabled state is not possible, this function throws an assert.
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}

/**
 * \brief Set PA1 input/sense configuration
 *
 * Enable/disable PA1 digital input buffer and pin change interrupt,
 * select pin interrupt edge/level sensing mode
 *
 * \param[in] isc PORT_ISC_INTDISABLE_gc    = Iterrupt disabled but input buffer enabled
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}

/**
 * \brief Set PA1 inverted mode
 *
 * Enable or disable inverted I/O on a pin
 *
 * \param[in] inverted true  = I/O on PA1 is inverted
 *                     false = I/O on PA1 is not inverted
 */
static inline void PA1_set_inverted(const bool inverted)
{
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}

/**
 * \brief Set PA1 level
 *
 * Sets output level on a pin
 *
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}

/**
 * \brief Toggle output level on PA1
 *
 * Toggle the pin level
 */
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}

/**
 * \brief Get level on PA1
 *
 * Reads the level on a pin
 */
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

/**
 * \brief Set PA4 pull mode
 *
 * Configure pin to pull up, down or disable pull mode, supported pull
 * modes are defined by device used
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}

/**
 * \brief Set PA4 data direction
 *
 * Select if the pin data direction is input, output or disabled.
 * If disabled state is not possible, this function throws an assert.
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}

/**
 * \brief Set PA4 input/sense configuration
 *
 * Enable/disable PA0 digital input buffer and pin change interrupt,
 * select pin interrupt edge/level sensing mode
 *
 * \param[in] isc PORT_ISC_INTDISABLE_gc    = Iterrupt disabled but input buffer enabled
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}

/**
 * \brief Set PA4 inverted mode
 *
 * Enable or disable inverted I/O on a pin
 *
 * \param[in] inverted true  = I/O on PA0 is inverted
 *                     false = I/O on PA0 is not inverted
 */
static inline void PA4_set_inverted(const bool inverted)
{
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}

/**
 * \brief Set PA4 level
 *
 * Sets output level on a pin
 *
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}

/**
 * \brief Toggle output level on PA4
 *
 * Toggle the pin level
 */
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}

/**
 * \brief Get level on PA4
 *
 * Reads the level on a pin
 */
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}

/**
 * \brief Set PA5 pull mode
 *
 * Configure pin to pull up, down or disable pull mode, supported pull
 * modes are defined by device used
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}

/**
 * \brief Set PA5 data direction
 *
 * Select if the pin data direction is input, output or disabled.
 * If disabled state is not possible, this function throws an assert.
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}

/**
 * \brief Set PA5 input/sense configuration
 *
 * Enable/disable PA5 digital input buffer and pin change interrupt,
 * select pin interrupt edge/level sensing mode
 *
 * \param[in] isc PORT_ISC_INTDISABLE_gc    = Interrupt disabled but input buffer enabled
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}

/**
 * \brief Set PA5 inverted mode
 *
 * Enable or disable inverted I/O on a pin
 *
 * \param[in] inverted true  = I/O on PA1 is inverted
 *                     false = I/O on PA1 is not inverted
 */
static inline void PA5_set_inverted(const bool inverted)
{
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}

/**
 * \brief Set PA5 level
 *
 * Sets output level on a pin
 *
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}

/**
 * \brief Toggle output level on PA5
 *
 * Toggle the pin level
 */
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}

/**
 * \brief Get level on PA5
 *
 * Reads the level on a pin
 */
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}

/**
 * \brief Set PC0 pull mode
 *
 * Configure pin to pull up, down or disable pull mode, supported pull
 * modes are defined by device used
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}

/**
 * \brief Set PC0 data direction
 *
 * Select if the pin data direction is input, output or disabled.
 * If disabled state is not possible, this function throws an assert.
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}

/**
 * \brief Set PC0 input/sense configuration
 *
 * Enable/disable PC0 digital input buffer and pin change interrupt,
 * select pin interrupt edge/level sensing mode
 *
 * \param[in] isc PORT_ISC_INTDISABLE_gc    = Iterrupt disabled but input buffer enabled
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}

/**
 * \brief Set PC0 inverted mode
 *
 * Enable or disable inverted I/O on a pin
 *
 * \param[in] inverted true  = I/O on PC0 is inverted
 *                     false = I/O on PC0 is not inverted
 */
static inline void PC0_set_inverted(const bool inverted)
{
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}

/**
 * \brief Set PC0 level
 *
 * Sets output level on a pin
 *
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}

/**
 * \brief Toggle output level on PC0
 *
 * Toggle the pin level
 */
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}

/**
 * \brief Get level on PC0
 *
 * Reads the level on a pin
 */
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}

/**
 * \brief Set PC1 pull mode
 *
 * Configure pin to pull up, down or disable pull mode, supported pull
 * modes are defined by device used
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}

/**
 * \brief Set PC1 data direction
 *
 * Select if the pin data direction is input, output or disabled.
 * If disabled state is not possible, this function throws an assert.
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}

/**
 * \brief Set PC1 input/sense configuration
 *
 * Enable/disable PC1 digital input buffer and pin change interrupt,
 * select pin interrupt edge/level sensing mode
 *
 * \param[in] isc PORT_ISC_INTDISABLE_gc    = Iterrupt disabled but input buffer enabled
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}

/**
 * \brief Set PC1 inverted mode
 *
 * Enable or disable inverted I/O on a pin
 *
 * \param[in] inverted true  = I/O on PC1 is inverted
 *                     false = I/O on PC1 is not inverted
 */
static inline void PC1_set_inverted(const bool inverted)
{
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}

/**
 * \brief Set PC1 level
 *
 * Sets output level on a pin
 *
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}

/**
 * \brief Toggle output level on PC1
 *
 * Toggle the pin level
 */
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}

/**
 * \brief Get level on PC1
 *
 * Reads the level on a pin
 */
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

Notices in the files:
SignalSlinger/KiCad/SignalSlinger/SignalSlinger.kicad_pcb:
Open Source: MIT License
